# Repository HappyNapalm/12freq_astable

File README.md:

# 12freq_astable
KiCAD files used to design and manufacture a series of astable multivibrators that operate in audible frequencies

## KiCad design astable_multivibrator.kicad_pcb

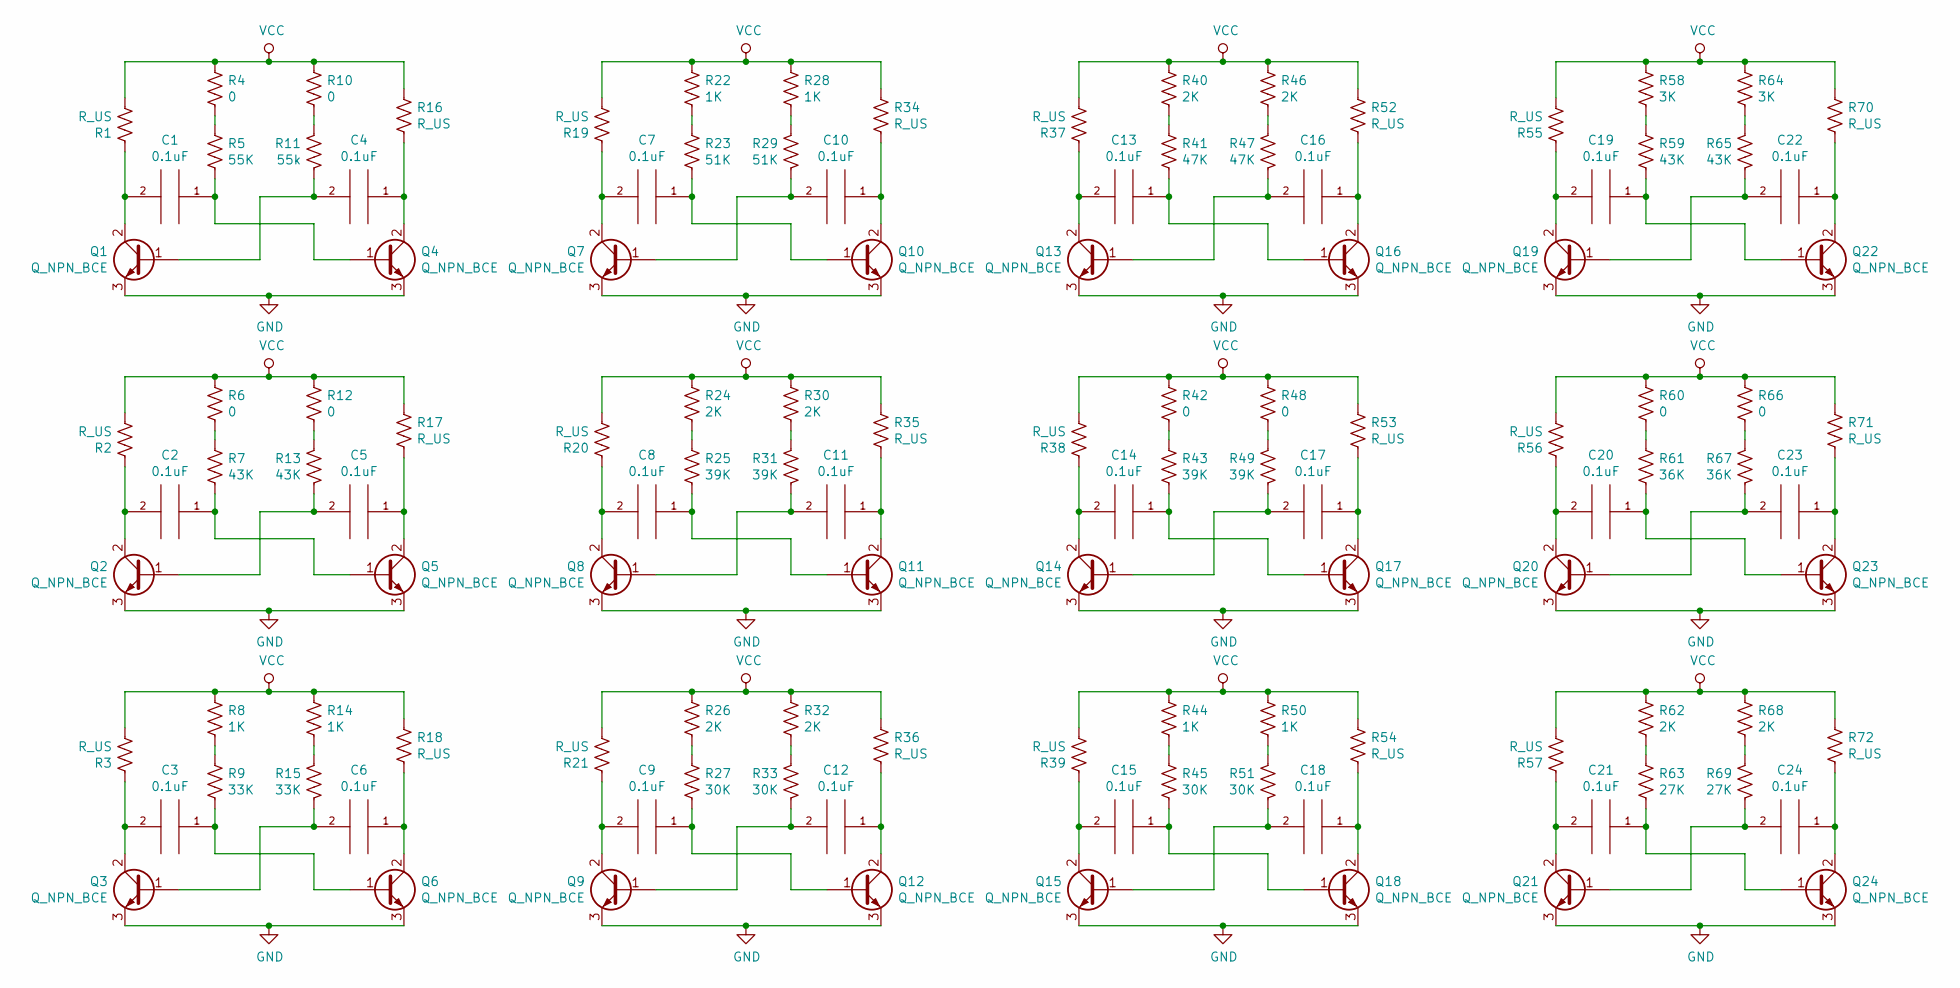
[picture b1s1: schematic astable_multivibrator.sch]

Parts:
C1, C2, C3, C4, C5, C6, C7, C8, C9, C10, C11, C12, C13, C14, C15, C16, C17, C18, C19, C20, C21, C22, C23, C24: 0.1uF; C_0805_2012Metric_Pad1.15x1.40mm_HandSolder
Q1, Q2, Q3, Q4, Q5, Q6, Q7, Q8, Q9, Q10, Q11, Q12, Q13, Q14, Q15, Q16, Q17, Q18, Q19, Q20, Q21, Q22, Q23, Q24: Q_NPN_BCE; SOT-23-6_Handsoldering
R1, R2, R3, R16, R17, R18, R19, R20, R21, R34, R35, R36, R37, R38, R39, R52, R53, R54, R55, R56, R57, R70, R71, R72: R_US; R_Axial_DIN0204_L3.6mm_D1.6mm_P5.08mm_Horizontal
R4, R6, R10, R12, R42, R48, R60, R66: 0; R_Axial_DIN0204_L3.6mm_D1.6mm_P5.08mm_Horizontal
R5: 55K; R_Axial_DIN0204_L3.6mm_D1.6mm_P5.08mm_Horizontal
R7, R13, R59, R65: 43K; R_Axial_DIN0204_L3.6mm_D1.6mm_P5.08mm_Horizontal
R8, R14, R22, R28, R44, R50: 1K; R_Axial_DIN0204_L3.6mm_D1.6mm_P5.08mm_Horizontal
R9, R15: 33K; R_Axial_DIN0204_L3.6mm_D1.6mm_P5.08mm_Horizontal
R11: 55k; R_Axial_DIN0204_L3.6mm_D1.6mm_P5.08mm_Horizontal
R23, R29: 51K; R_Axial_DIN0204_L3.6mm_D1.6mm_P5.08mm_Horizontal
R24, R26, R30, R32, R40, R46, R62, R68: 2K; R_Axial_DIN0204_L3.6mm_D1.6mm_P5.08mm_Horizontal
R25, R31, R43, R49: 39K; R_Axial_DIN0204_L3.6mm_D1.6mm_P5.08mm_Horizontal
R27, R33, R45, R51: 30K; R_Axial_DIN0204_L3.6mm_D1.6mm_P5.08mm_Horizontal
R41, R47: 47K; R_Axial_DIN0204_L3.6mm_D1.6mm_P5.08mm_Horizontal
R58, R64: 3K; R_Axial_DIN0204_L3.6mm_D1.6mm_P5.08mm_Horizontal
R61, R67: 36K; R_Axial_DIN0204_L3.6mm_D1.6mm_P5.08mm_Horizontal
R63, R69: 27K; R_Axial_DIN0204_L3.6mm_D1.6mm_P5.08mm_Horizontal

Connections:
GND: Q1.3 (E), Q2.3 (E), Q3.3 (E), Q4.3 (E), Q5.3 (E), Q6.3 (E), Q7.3 (E), Q8.3 (E), Q9.3 (E), Q10.3 (E), Q11.3 (E), Q12.3 (E), Q13.3 (E), Q14.3 (E), Q15.3 (E), Q16.3 (E), Q17.3 (E), Q18.3 (E), Q19.3 (E), Q20.3 (E), Q21.3 (E), Q22.3 (E), Q23.3 (E), Q24.3 (E)
unnamed: C1.1, Q4.1 (B), R5.2
unnamed: C1.2, Q1.2 (C), R1.1
unnamed: C2.1, Q5.1 (B), R7.2
unnamed: C2.2, Q2.2 (C), R2.1
unnamed: C3.1, Q6.1 (B), R9.2
unnamed: C3.2, Q3.2 (C), R3.1
unnamed: C4.1, Q4.2 (C), R16.2
unnamed: C4.2, Q1.1 (B), R11.1
unnamed: C5.1, Q5.2 (C), R17.2
unnamed: C5.2, Q2.1 (B), R13.1
unnamed: C6.1, Q6.2 (C), R18.2
unnamed: C6.2, Q3.1 (B), R15.1
unnamed: C7.1, Q10.1 (B), R23.2
unnamed: C7.2, Q7.2 (C), R19.1
unnamed: C8.1, Q11.1 (B), R25.2
unnamed: C8.2, Q8.2 (C), R20.1
unnamed: C9.1, Q12.1 (B), R27.2
unnamed: C9.2, Q9.2 (C), R21.1
unnamed: C10.1, Q10.2 (C), R34.2
unnamed: C10.2, Q7.1 (B), R29.1
unnamed: C11.1, Q11.2 (C), R35.2
unnamed: C11.2, Q8.1 (B), R31.1
unnamed: C12.1, Q12.2 (C), R36.2
unnamed: C12.2, Q9.1 (B), R33.1
unnamed: C13.1, Q16.1 (B), R41.2
unnamed: C13.2, Q13.2 (C), R37.1
unnamed: C14.1, Q17.1 (B), R43.2
unnamed: C14.2, Q14.2 (C), R38.1
unnamed: C15.1, Q18.1 (B), R45.2
unnamed: C15.2, Q15.2 (C), R39.1
unnamed: C16.1, Q16.2 (C), R52.2
unnamed: C16.2, Q13.1 (B), R47.1
unnamed: C17.1, Q17.2 (C), R53.2
unnamed: C17.2, Q14.1 (B), R49.1
unnamed: C18.1, Q18.2 (C), R54.2
unnamed: C18.2, Q15.1 (B), R51.1
unnamed: C19.1, Q22.1 (B), R59.2
unnamed: C19.2, Q19.2 (C), R55.1
unnamed: C20.1, Q23.1 (B), R61.2
unnamed: C20.2, Q20.2 (C), R56.1
unnamed: C21.1, Q24.1 (B), R63.2
unnamed: C21.2, Q21.2 (C), R57.1
unnamed: C22.1, Q22.2 (C), R70.2
unnamed: C22.2, Q19.1 (B), R65.1
unnamed: C23.1, Q23.2 (C), R71.2
unnamed: C23.2, Q20.1 (B), R67.1
unnamed: C24.1, Q24.2 (C), R72.2
unnamed: C24.2, Q21.1 (B), R69.1
unnamed: R4.2, R5.1
unnamed: R6.2, R7.1
unnamed: R8.2, R9.1
unnamed: R10.1, R11.2
unnamed: R12.1, R13.2
unnamed: R14.1, R15.2
unnamed: R22.2, R23.1
unnamed: R24.2, R25.1
unnamed: R26.2, R27.1
unnamed: R28.1, R29.2
unnamed: R30.1, R31.2
unnamed: R32.1, R33.2
unnamed: R40.2, R41.1
unnamed: R42.2, R43.1
unnamed: R44.2, R45.1
unnamed: R46.1, R47.2
unnamed: R48.1, R49.2
unnamed: R50.1, R51.2
unnamed: R58.2, R59.1
unnamed: R60.2, R61.1
unnamed: R62.2, R63.1
unnamed: R64.1, R65.2
unnamed: R66.1, R67.2
unnamed: R68.1, R69.2
VCC: R1.2, R2.2, R3.2, R4.1, R6.1, R8.1, R10.2, R12.2, R14.2, R16.1, R17.1, R18.1, R19.2, R20.2, R21.2, R22.1, R24.1, R26.1, R28.2, R30.2, R32.2, R34.1, R35.1, R36.1, R37.2, R38.2, R39.2, R40.1, R42.1, R44.1, R46.2, R48.2, R50.2, R52.1, R53.1, R54.1, R55.2, R56.2, R57.2, R58.1, R60.1, R62.1, R64.2, R66.2, R68.2, R70.1, R71.1, R72.1

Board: 2 copper layers, 120 parts (0 on the bottom side), 74 nets, no tracks yet.

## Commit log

2021-10-08 finished the schematic
2021-10-08 generated netlist and imported netlist into pcb.
2021-10-08 added speaker and usb-mini power plug to schematic.
2022-01-08 Added switches to schematic and labeling to both schematic and PCB
